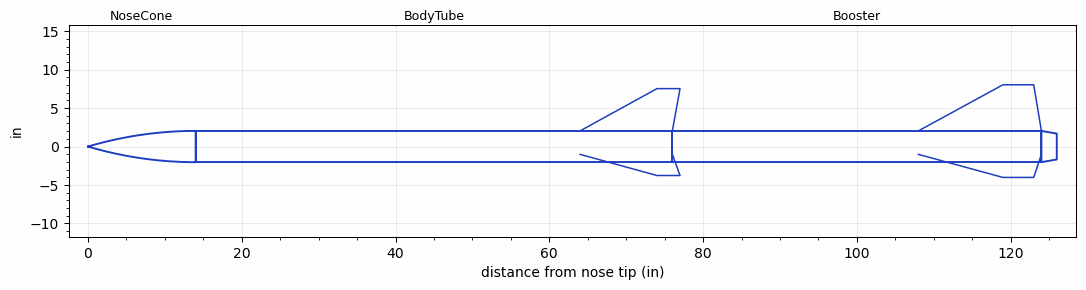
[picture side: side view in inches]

<RASAeroDocument>
 <FileVersion>2</FileVersion>
 <RocketDesign>
  <NoseCone>
   <Length>14</Length>
   <Diameter>4.069</Diameter>
   <Shape>Tangent Ogive</Shape>
   <Location>0</Location>
  </NoseCone>
  <BodyTube>
   <Length>62</Length>
   <Diameter>4.069</Diameter>
   <RailGuideDiameter>0.25</RailGuideDiameter>
   <RailGuideHeight>0.25</RailGuideHeight>
   <Location>14</Location>
   <Fin>
    <Count>3</Count>
    <Chord>12</Chord>
    <Span>5.5</Span>
    <SweepDistance>10</SweepDistance>
    <TipChord>3</TipChord>
    <Thickness>0.21</Thickness>
    <LERadius>0.02</LERadius>
    <Location>12</Location>
    <AirfoilSection>Hexagonal</AirfoilSection>
    <FX1>1</FX1>
    <FX3>0.49</FX3>
   </Fin>
  </BodyTube>
  <Booster>
   <Length>48</Length>
   <Diameter>4.069</Diameter>
   <InsideDiameter>4.069</InsideDiameter>
   <RailGuideDiameter>0.25</RailGuideDiameter>
   <RailGuideHeight>0.25</RailGuideHeight>
   <Location>76</Location>
   <ShoulderLength>0</ShoulderLength>
   <BoattailLength>2</BoattailLength>
   <BoattailRearDiameter>3.36</BoattailRearDiameter>
   <Fin>
    <Count>3</Count>
    <Chord>16</Chord>
    <Span>6</Span>
    <SweepDistance>11</SweepDistance>
    <TipChord>4</TipChord>
    <Thickness>0.21</Thickness>
    <LERadius>0.02</LERadius>
    <Location>16</Location>
    <AirfoilSection>Hexagonal</AirfoilSection>
    <FX1>1</FX1>
    <FX3>0.49</FX3>
   </Fin>
  </Booster>
  <Surface>Camouflage Paint</Surface>
  <ModifiedBarrowman>True</ModifiedBarrowman>
  <Turbulence>False</Turbulence>
  <UseBooster1>False</UseBooster1>
  <UseBooster2>False</UseBooster2>
 </RocketDesign>
 <LaunchSite>
  <Altitude>800</Altitude>
  <Pressure>0</Pressure>
  <RodAngle>2</RodAngle>
  <RodLength>12</RodLength>
  <Temperature>75</Temperature>
  <WindSpeed>10</WindSpeed>
 </LaunchSite>
 <Recovery>
  <Altitude1>1000</Altitude1>
  <Altitude2>800</Altitude2>
  <DeviceType1>Parachute</DeviceType1>
  <DeviceType2>Parachute</DeviceType2>
  <Event1>True</Event1>
  <Event2>True</Event2>
  <Size1>42</Size1>
  <Size2>90</Size2>
  <EventType1>Apogee</EventType1>
  <EventType2>Altitude</EventType2>
  <CD1>0.7</CD1>
  <CD2>0.85</CD2>
 </Recovery>
 <SimulationList>
  <Simulation>
   <SustainerEngine>L1736  (GOW)</SustainerEngine>
   <SustainerLaunchWt>20.7</SustainerLaunchWt>
   <SustainerNozzleDiameter>1.675</SustainerNozzleDiameter>
   <SustainerCG>51.29</SustainerCG>
   <SustainerIgnitionDelay>1</SustainerIgnitionDelay>
   <Booster1Engine>L1736  (GOW)</Booster1Engine>
   <Booster1LaunchWt>40.8</Booster1LaunchWt>
   <Booster1SeparationDelay>0.2</Booster1SeparationDelay>
   <Booster1IgnitionDelay>0</Booster1IgnitionDelay>
   <Booster1CG>79.24</Booster1CG>
   <Booster1NozzleDiameter>1.675</Booster1NozzleDiameter>
   <IncludeBooster1>True</IncludeBooster1>
   <Booster2Delay>0</Booster2Delay>
   <IncludeBooster2>False</IncludeBooster2>
   <TimetoApogee>30.65055</TimetoApogee>
   <MaxAltitude>16494.61</MaxAltitude>
   <MaxVelocity>1579.507</MaxVelocity>
   <OptimumWt>15.648</OptimumWt>
   <OptimumMaxAlt>15.648</OptimumMaxAlt>
  </Simulation>
  <Simulation>
   <SustainerEngine>L1750  (GOW)</SustainerEngine>
   <SustainerLaunchWt>20.7</SustainerLaunchWt>
   <SustainerNozzleDiameter>1.675</SustainerNozzleDiameter>
   <SustainerCG>51.29</SustainerCG>
   <SustainerIgnitionDelay>1</SustainerIgnitionDelay>
   <Booster1Engine>L1750  (GOW)</Booster1Engine>
   <Booster1LaunchWt>40.8</Booster1LaunchWt>
   <Booster1SeparationDelay>0.4</Booster1SeparationDelay>
   <Booster1IgnitionDelay>0</Booster1IgnitionDelay>
   <Booster1CG>79.24</Booster1CG>
   <Booster1NozzleDiameter>1.675</Booster1NozzleDiameter>
   <IncludeBooster1>True</IncludeBooster1>
   <Booster2Delay>0</Booster2Delay>
   <IncludeBooster2>False</IncludeBooster2>
   <TimetoApogee>30.38054</TimetoApogee>
   <MaxAltitude>16122.63</MaxAltitude>
   <MaxVelocity>1567.886</MaxVelocity>
  </Simulation>
 </SimulationList>
</RASAeroDocument>
